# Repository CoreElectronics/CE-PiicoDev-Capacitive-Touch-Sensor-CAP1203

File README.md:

# PiicoDev® Capacitive Touch Sensor CAP1203

This is the repo for the Core Electronics [PiicoDev Capacitive Touch Sensor CAP1203](https://core-electronics.com.au/catalog/product/view/sku/CE07816).

The PiicoDev® Capacitive Touch Sensor gives your project three touch pads to use as inputs. This is an effective way to introduce control inputs to your project.  Get creative and use other items as touch plates using PCB headers or the alligator clip connection holes.

- 3 Capacitive Touch Sensor inputs
- Supports simultaneous touch events
- Programmable sensitivity
- Automatically calibrates at powerup
- Activity LED shows interrupt events
- PiicoDev connector, compatible with Qwiic and STEMMA QT (3.3V only)
- 2.54mm breakout for breadboarding/prototyping
- Manufactured and supported in Australia by Core Electronics

Getting Started Guides

- For [Micro:bit](https://core-electronics.com.au/tutorials/raspberry-pi-pico/piicodev-capacitive-touch-sensor-cap1203-micro-bit-guide.html)
- For [Raspberry Pi Pico](https://core-electronics.com.au/tutorials/raspberry-pi-pico/piicodev-capacitive-touch-sensor-cap1203-raspberry-pi-pico-guide.html)
- For [Raspberry Pi](https://core-electronics.com.au/tutorials/raspberry-pi-pico/piicodev-capacitive-touch-sensor-cap1203-raspberry-pi-guide.html)

# License
This project is open source - please review the LICENSE.md file for further licensing information.

If you have any technical questions, or concerns about licensing, please contact technical support on the [Core Electronics forums](https://forum.core-electronics.com.au/).

# Attribution
The hardware design of this module is influenced by the design from [Sparkfun](https://github.com/sparkfun/Qwiic_Capacitive_Touch_Slider_CAP1203).

*\"PiicoDev\" and the PiicoDev logo are trademarks of Core Electronics Pty Ltd.*

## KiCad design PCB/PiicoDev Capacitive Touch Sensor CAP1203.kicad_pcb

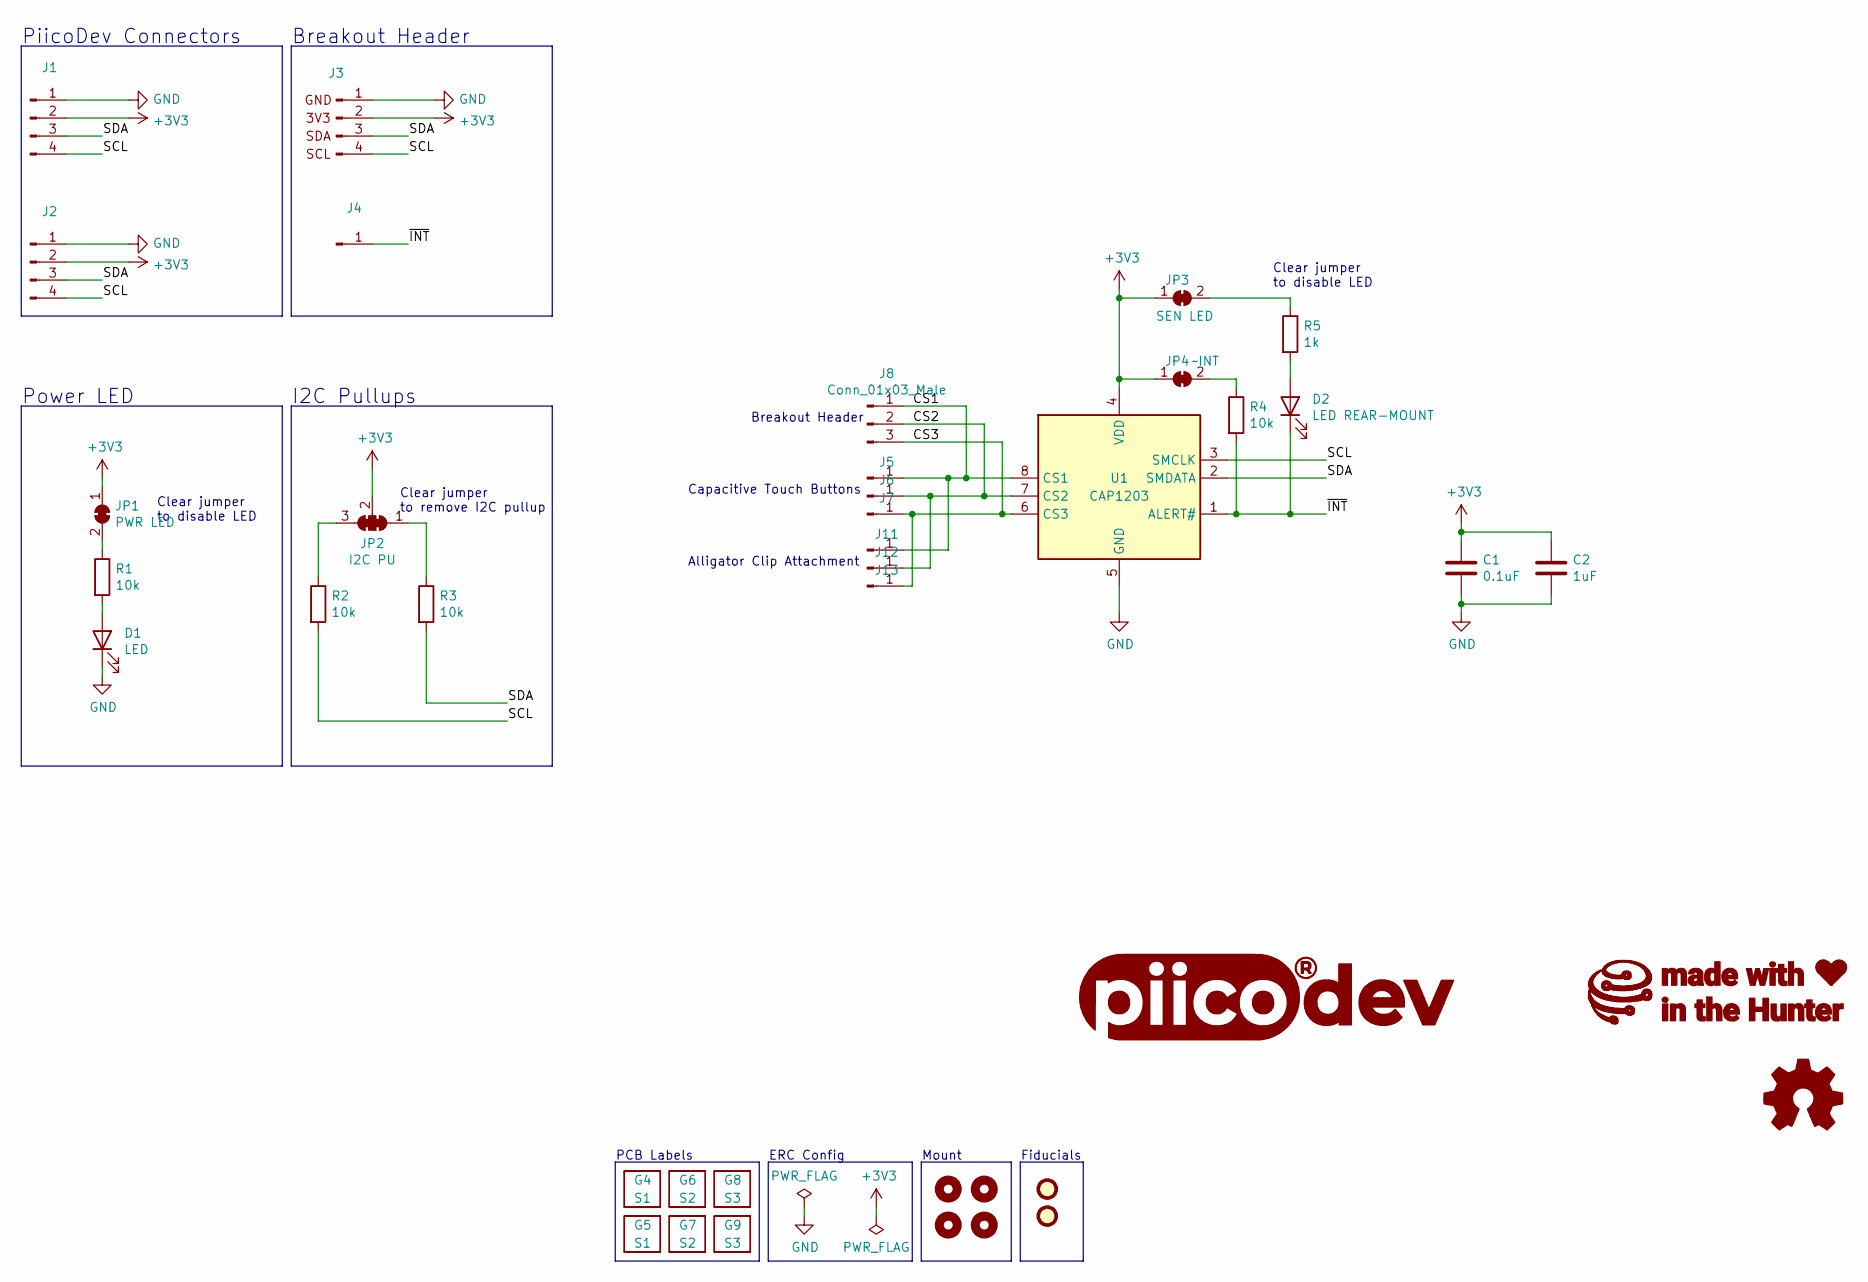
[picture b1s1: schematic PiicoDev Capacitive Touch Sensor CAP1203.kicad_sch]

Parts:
C1: 0.1uF; C_0402_1005Metric
C2: 1uF; C_0402_1005Metric
D1: LED; LED_0603_1608Metric
D2: LED REAR-MOUNT; LED_1206_3216Metric_ReverseMount_Hole1.8x2.4mm
FID1, FID2: Fiducial; Fiducial_1mm_Mask2mm
G1: LOGO_PiicoDev; piicodev_logo_14.2x3.4mm
G2: LOGO_CoreElectronics_no-text; CoreElectronics_logo_5mm
G3: LOGO_made-with-love; piicodev_logo_14.2x3.4mm
G4, G5: S1; Label_S1_Reverse
G6, G7: S2; Label_S2_Reverse
G8, G9: S3; Label_S3_Reverse
H1, H2, H3, H4: MountingHole; MountingHole_2.7mm_M2.5_PadClearance_1.2
J1, J2: JST_SH_SM04B-SRSS-TB_1x04-1MP_P1.00mm_Horizontal
J3: Conn_PiicoDev_header_01x04_Male; PiicoDev_header_4pin
J4: Conn_01x01_Male; PiicoDev_header_1pin_INT_inverted
J5, J6, J7: Conn_01x01_Male; Capacitive_Touch_Button
J8: Conn_01x03_Male; PinHeader_1x03_P2.54mm_Vertical
J11, J12, J13: Conn_01x01_Male; Conn_alligator
JP1: PWR LED; SolderJumper-2_P1.3mm_Bridged_RoundedPad1.0x1.5mm
JP2: I2C PU; SolderJumper-3_P1.3mm_Closed_RoundedPad1.0x1.5mm_NumberLabe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
JP3: SEN LED; SolderJumper-2_P1.3mm_Bridged_RoundedPad1.0x1.5mm
JP4: ~INT; SolderJumper-2_P1.3mm_Bridged_RoundedPad1.0x1.5mm
LOGO1: Logo_Open_Hardware_Small; oshw
R1, R2, R3, R4: 10k; R_0402_1005Metric
R5: 1k; R_0402_1005Metric
U1: CAP1203; SOIC-8_3.9x4.9mm_P1.27mm

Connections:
+3V3: C1.1, C2.1, J1.2, J2.2, J3.2, JP1.1 (A), JP2.2 (C), JP3.1 (A), JP4.1 (A), U1.4 (VDD)
/CS1: J5.1, J8.1, J11.1, U1.8 (CS1)
/CS2: J6.1, J8.2, J12.1, U1.7 (CS2)
/CS3: J7.1, J8.3, J13.1, U1.6 (CS3)
/SCL: J1.4, J2.4, J3.4, R2.2, U1.3 (SMCLK)
/SDA: J1.3, J2.3, J3.3, R3.2, U1.2 (SMDATA)
/~INT: D2.1 (K), J4.1, R4.2, U1.1 (ALERT#)
GND: C1.2, C2.2, D1.1 (K), J1.1, J2.1, J3.1, U1.5 (GND)
unnamed: D1.2 (A), R1.2
unnamed: D2.2 (A), R5.2
unnamed: JP1.2 (B), R1.1
unnamed: JP2.1 (A), R3.1
unnamed: JP2.3 (B), R2.1
unnamed: JP3.2 (B), R5.1
unnamed: JP4.2 (B), R4.1

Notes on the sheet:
Power LED
I2C Pullups
Capacitive Touch Buttons
Clear jumper to remove I2C pullup
Breakout Header
Alligator Clip Attachment
ERC Config
Mount
PCB Labels
PiicoDev Connectors
Clear jumper to disable LED
Fiducials

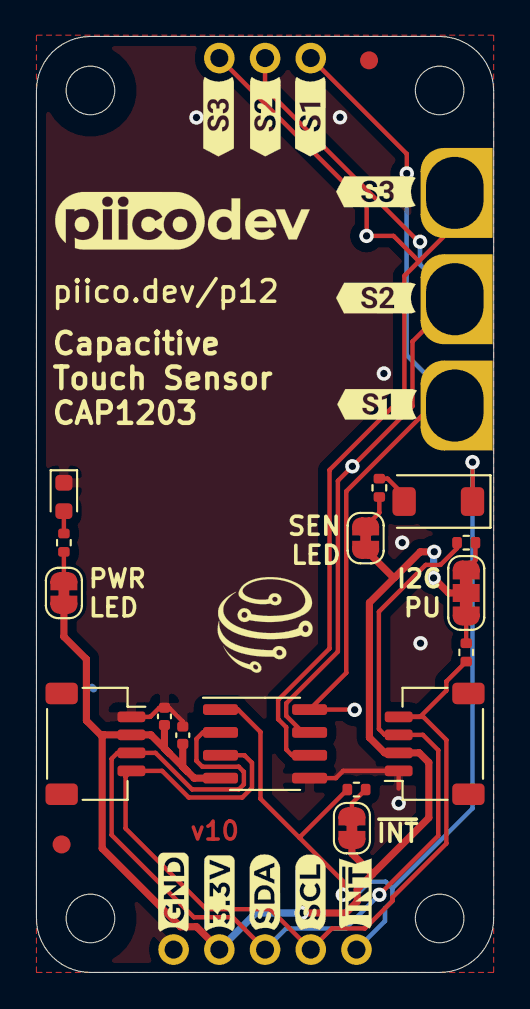
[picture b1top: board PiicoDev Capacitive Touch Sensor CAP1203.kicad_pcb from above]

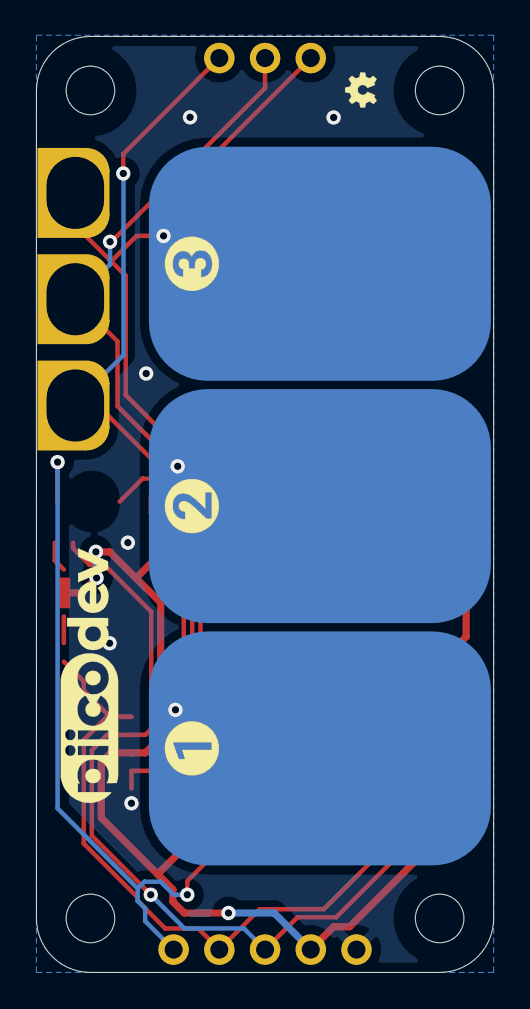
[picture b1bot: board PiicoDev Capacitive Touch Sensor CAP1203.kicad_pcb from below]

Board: 2 copper layers, 25.4 x 52.0 mm, 41 parts (7 on the bottom side), 15 nets.

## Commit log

2021-06-09 Update interrupt LED and increase alligator clip hole size
2021-06-21 Add silk screen labels
2021-06-23 Increase Alligator Clip Size
2021-06-24 Change top copper fill from grounded to floating sections
2021-07-08 Revert "Change top copper fill from grounded to floating sections"
    This reverts commit 368bc0d4ff66a5d992a58d852e4a1f950c0b97f4.
2021-07-08 Update version number for production
2021-08-24 Change R1 resistor value
2021-12-08 Update R1,2,3,4 to 10k
2022-01-25 Update user drawings - dimensioning
2022-03-21 Update schematic-piicodev-capacitive-touch-sensor-cap1203-v10.pdf
    resistors 4k7 to 10k
2022-05-11 Upgrade to KiCad 6.0.5
2022-05-11 upgrade to KiCad6
2022-05-12 add image

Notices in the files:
PCB/PiicoDev Capacitive Touch Sensor CAP1203.kicad_sch:
License: CCASAv4.0 http://creativecommons.org/licenses/by-sa/4.0
